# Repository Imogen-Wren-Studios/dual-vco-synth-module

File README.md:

# noise-synth-oscillator

## Preliminary Renderings

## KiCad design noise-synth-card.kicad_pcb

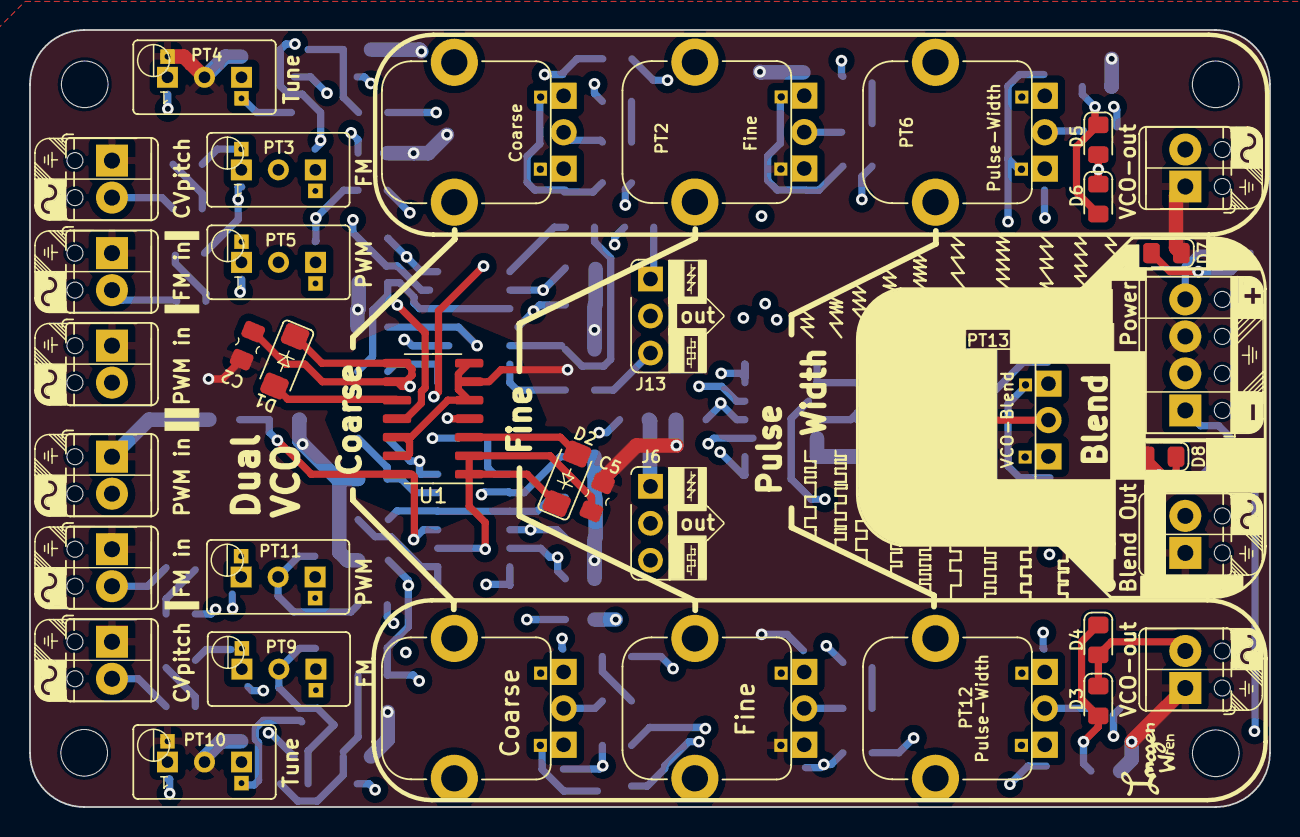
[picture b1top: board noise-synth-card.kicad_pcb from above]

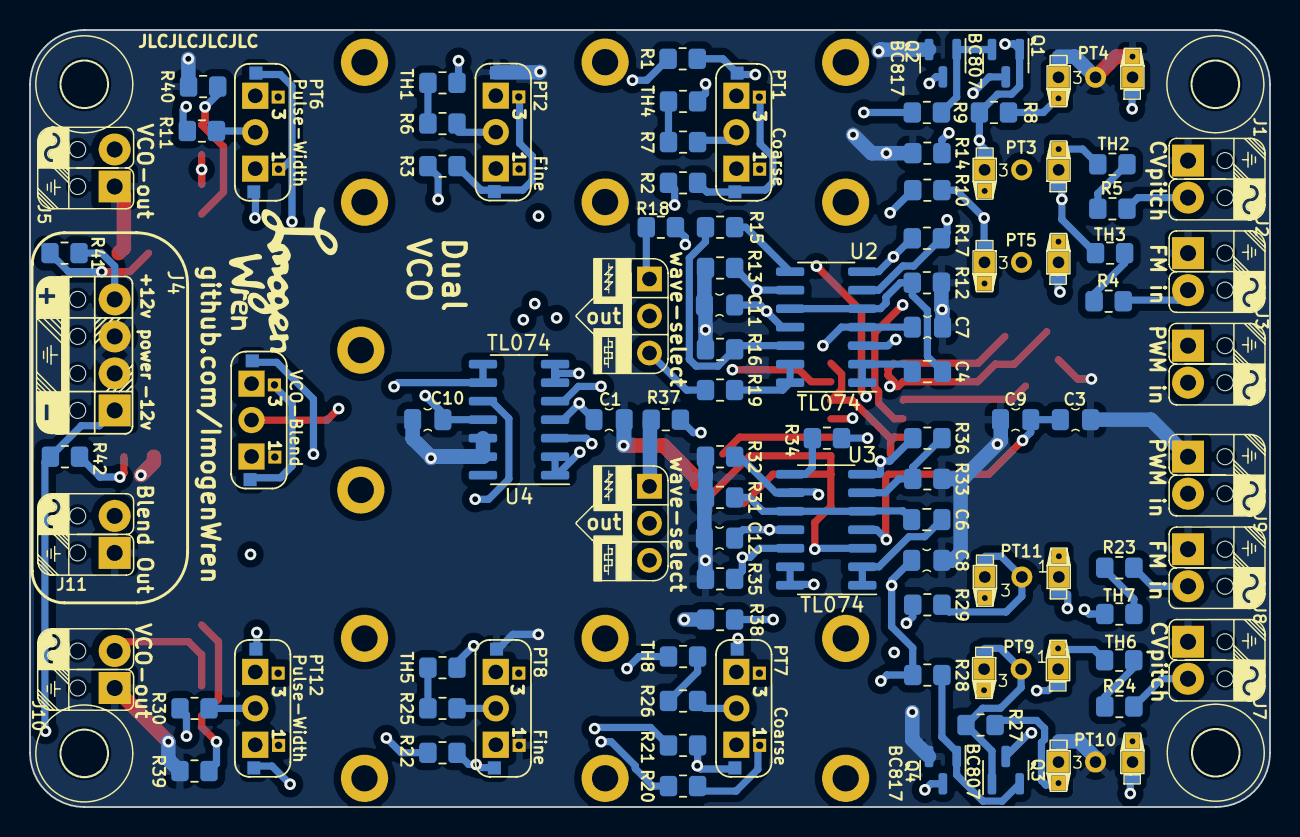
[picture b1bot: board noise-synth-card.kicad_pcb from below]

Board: 4 copper layers, 85.1 x 53.3 mm, 104 parts (68 on the bottom side), 73 nets.

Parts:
C1, C3, C7, C8, C10, C11, C12: 100n; C_0805_2012_HandSolder_kawaii
C2, C5: 2n2; C_0805_2012_HandSolder_kawaii
C4, C6: 1u; C_0805_2012Metric_Pad1.18x1.45mm_HandSolder
C9: 100p; C_0805_2012_HandSolder_kawaii
D1, D2: 1N4148_SMD_quatromelf; D_MiniMELF_kawaii
D3, D4: pink; LED_0805_2012_Kawaii
D5, D6, D8: blue; LED_0805_2012_Kawaii
D7: green; LED_0805_2012_Kawaii
J1, J7: CVpitch; synth-signal-MPT-0,5-2-2.54_1x02_P2.54mm_Horizontal
J2, J8: FM in; synth-signal-MPT-0,5-2-2.54_1x02_P2.54mm_Horizontal
J3, J9: PWM in; synth-signal-MPT-0,5-2-2.54_1x02_P2.54mm_Horizontal
J4: power; synth-power-termbox-MPT-0,5-4-2.54_1x04_P2.54mm
J5, J10: VCO-out; synth-signal-MPT-0,5-2-2.54_1x02_P2.54mm_Horizontal
J6, J13: wave-select; 2-way-select
J11: Blend Out; synth-signal-MPT-0,5-2-2.54_1x02_P2.54mm_Horizontal
M1: imogen-wren-card; credit-card-screws
PT1, PT2, PT6, PT7, PT8, PT12: 100k; Potentiometer_Alpha-reversable
PT3, PT9: 1M; Potentiometer_Bourns-reversable-1
PT4, PT10: 1k; Potentiometer_Bourns-reversable-1
PT5, PT11: 250k; Potentiometer_Bourns-reversable-1
PT13: 1M; Potentiometer_Alpha-reversable
Q1, Q3: BC807; SOT-23
Q2, Q4: BC817; SOT-23
R1, R3, R4, R5, R7, R11, R12, R15, R17, R20, R22, R23, R24, R26, R30, R31, R34, R36: 100k; R_0805_2012Metric_Pad1.20x1.40mm_HandSolder
R2, R21: 33k; R_0805_2012Metric_Pad1.20x1.40mm_HandSolder
R6, R9, R25, R28: 1M; R_0805_2012Metric_Pad1.20x1.40mm_HandSolder
R8, R27: 1k5; R_0805_2012Metric_Pad1.20x1.40mm_HandSolder
R10, R16, R29, R35: 68k; R_0805_2012Metric_Pad1.20x1.40mm_HandSolder
R13, R32: 14k; R_0805_2012Metric_Pad1.20x1.40mm_HandSolder
R14, R33: 47k; R_0805_2012Metric_Pad1.20x1.40mm_HandSolder
R18, R19, R37, R38, R39, R40, R41, R42: 1k; R_0805_2012Metric_Pad1.20x1.40mm_HandSolder
TH1, TH2, TH3, TH4, TH5, TH6, TH7, TH8: 10k; Resistor_0805_2012_handsolder
U1: HEF4093B; SOIC-14_3.9x8.7mm_P1.27mm
U2, U3, U4: TL074; SOIC-14_3.9x8.7mm_P1.27mm

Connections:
+12V: C1.1, C3.1, C7.1, C8.1, C9.2, J4.4 (+12v), PT6.3, PT12.3, R1.2, R9.2, R20.2, R28.2, R41.2, U1.14 (VCC), U2.4 (V+), U3.4 (V+), U4.4 (V+)
-12V: C10.2, C11.2, C12.2, J4.1 (-12v), PT6.1, PT12.1, Q1.3 (C), Q3.3 (C), R2.1, R3.1, R21.1, R22.1, R42.2, U2.11 (V-), U3.11 (V-), U4.11 (V-)
/VCO-saw-square-0/VCO_OUT: D5.2 (A), D6.1 (K), J5.2 (signal), J13.2 (out), U4.5 (+)
/VCO-saw-square-1/VCO_OUT: D3.1 (K), D4.2 (A), J6.2 (out), J10.2 (signal), U4.10 (+)
GND: C1.2, C2.2, C3.2, C5.2, C7.2, C8.2, C9.1, C10.1, C11.1, C12.1, D7.1 (K), D8.2 (A), J1.1 (gnd), J2.1 (gnd), J3.1 (gnd), J4.2 (gnd), J4.3 (gnd), J5.1 (gnd), J7.1 (gnd), J8.1 (gnd), J9.1 (gnd), J10.1 (gnd), J11.1 (gnd), PT2.1, PT4.1, PT4.2, PT8.1, PT10.1, PT10.2, Q2.2 (E), Q4.2 (E), R12.1, R13.1, R14.1, R16.1, R31.1, R32.1, R33.1, R35.1, R39.1, R40.1, U1.5, U1.6, U1.7 (GND), U1.12, U1.13, U4.12 (+), U4.13 (-)
unnamed: D1.2 (A), U1.10
unnamed: C2.1, D1.1 (K), Q2.3 (C), U1.8, U1.9, U2.3 (+)
unnamed: D2.2 (A), U1.3
unnamed: C5.1, D2.1 (K), Q4.3 (C), U1.1, U1.2, U3.3 (+)
unnamed: D3.2 (A), D4.1 (K), R39.2
unnamed: D5.1 (K), D6.2 (A), R40.2
unnamed: D7.2 (A), R41.1
unnamed: D8.1 (K), R42.1
unnamed: J1.2 (signal), R5.1
unnamed: J2.2 (signal), R4.1
unnamed: J3.2 (signal), PT5.3
unnamed: J6.1 (saw), R37.2
unnamed: J6.3 (square), R38.2
unnamed: J7.2 (signal), R24.1
unnamed: J8.2 (signal), R23.1
unnamed: J9.2 (signal), PT11.3
unnamed: J11.2 (signal), U4.1, U4.2 (-)
unnamed: J13.1 (saw), R18.2
unnamed: J13.3 (square), R19.2
unnamed: PT1.1, R1.1
unnamed: PT1.2, R7.1
unnamed: PT1.3, R2.2
unnamed: PT2.2, R6.1
unnamed: PT2.3, R3.2
unnamed: PT3.3, TH3.2
unnamed: PT4.3, R8.1
unnamed: PT5.1, PT5.2, R10.1
unnamed: PT6.2, R11.1
unnamed: PT7.1, R20.1
unnamed: PT7.2, R26.1
unnamed: PT7.3, R21.2
unnamed: PT8.2, R25.1
unnamed: PT8.3, R22.2
unnamed: PT9.3, TH7.2
unnamed: PT10.3, R27.1
unnamed: PT11.1, PT11.2, R29.1
unnamed: PT12.2, R30.1
unnamed: PT3.1, PT3.2, Q1.1 (B), R8.2, TH1.2, TH2.2, TH4.2
unnamed: Q1.2 (E), Q2.1 (B), R9.1
unnamed: PT9.1, PT9.2, Q3.1 (B), R27.2, TH5.2, TH6.2, TH8.2
unnamed: Q3.2 (E), Q4.1 (B), R28.1
unnamed: R4.2, TH3.1
unnamed: R5.2, TH2.1
unnamed: R6.2, TH1.1
unnamed: R7.2, TH4.1
unnamed: R15.2, U2.8
unnamed: R17.1, R18.1, U2.7
unnamed: R23.2, TH7.1
unnamed: R24.2, TH6.1
unnamed: R25.2, TH5.1
unnamed: R26.2, TH8.1
unnamed: R34.2, U3.8
unnamed: R36.1, R37.1, U3.7
unnamed: C4.1, U2.1, U2.2 (-)
unnamed: C4.2, R12.2, U2.5 (+), U2.10 (+)
unnamed: R14.2, R17.2, U2.6 (-)
unnamed: R10.2, R11.2, R13.2, U2.9 (-)
unnamed: R15.1, R16.2, U2.12 (+)
unnamed: R19.1, U2.13 (-), U2.14
unnamed: C6.1, U3.1, U3.2 (-)
unnamed: C6.2, R31.2, U3.5 (+), U3.10 (+)
unnamed: R33.2, R36.2, U3.6 (-)
unnamed: R29.2, R30.2, R32.2, U3.9 (-)
unnamed: R34.1, R35.2, U3.12 (+)
unnamed: R38.1, U3.13 (-), U3.14
unnamed: PT13.2, U4.3 (+)
unnamed: PT13.1, U4.6 (-), U4.7
unnamed: PT13.3, U4.8, U4.9 (-)

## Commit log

2023-08-18 6yju5tjutj
2023-08-18 finished v1.0 schematic
2023-08-19 dgfhdh
2023-08-20 fixed shcematic
2023-08-20 sdfsdf
2023-08-22 Added weird pot footprints
2023-08-22 sdgsdf
2023-08-22 rtertert
2023-08-23 dsvgfsdgds
2023-08-24 ewrtdergf
2023-08-24 dfgdrfghdf
2023-08-28 UFKIHGFI
2023-08-28 sdfes
2023-08-28 layout almost finished
2023-08-28 sdgdrfgdrfg
2023-08-29 dfgdfgd
2023-08-29 dsrfgerge
2023-08-30 sdfsdfs
2023-08-30 ,b ,mn
2023-08-30 sdfsdfdsf
2023-08-31 sdfgdfgd
2023-08-31 sdvsdvsd vs
2023-09-02 juihui
2023-09-03 finished version 1
2023-09-05 sdgfsdf
2023-09-05 wergerg
2023-09-14 dgtrfgv
2023-09-17 jhfvjhg
2025-01-22 moving laptops
